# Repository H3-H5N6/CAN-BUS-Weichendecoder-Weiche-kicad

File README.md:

# CAN-BUS Weichendecoder

## Serielle Console
Auf der seriellen Console kann man die Konfiguration einsehen und und die Modul-Id ändern.

Die Serielle Schnittstelle muss dazu auf 115200 gesetzt werden

## Konfigiratuion ansehen

Mit der Taste "p" wird die aktuelle Konfiguartion angezeigt. Beispiel:

```
==== CAN-Konfiguration ====
Version:       1
Status ID:     2
CAN ID: [0] => 811
CAN ID: [1] => 812
CAN ID: [2] => 813
CAN ID: [3] => 814
CAN ID: [4] => 815
CAN ID: [5] => 816
CAN ID: [6] => 817
CAN ID: [7] => 818
CAN ID: [8] => 819
CAN ID: [9] => 820
===========================
```

## Modul-Adresse ändern:

Mit der Eingabe &lt;i> + Nr + &lt;Return> kann die Modul-Adresse geändert werden.

```
Neue ID: 2
Setze neue Id: 2
```

Der Weichendecoder liefert regelmäßig seinen aktuellen Zustand

## Protocol

### IDs

* 100 Frames mit der Id 100 dient dem Verändern des Zustandes
* 200 Sendet den aktuellen Zustand des Decoders, wenn die im ersten Datafeld (u_int16) angegebene Moduladresse mit der des Moduls übereinstimmt. Der Status selbst wird mit der Id 300 gesendet

## CAN-Bus-RJ45-Steckerbelegung

Quelle: https://www.opendcc.de/info/can/can_connector.html

    CAN Pinbelegung auf RJ45
    RJ45 	
    Pin	Signal	    Beschreibung
    1 	CAN_H       Dominant High
    2 	CAN_L    	Dominant Low
    3 	CAN_GND     Ground
    4 	Reserved    Upgrade Path  // DCC A
    5 	Reserved    Upgrade Path  // DCC B
    6 	CAN_SHLD    CAN Shield, Optional
    7 	CAN_GND     Ground
    8 	CAN_V+ 	    Power, Optional

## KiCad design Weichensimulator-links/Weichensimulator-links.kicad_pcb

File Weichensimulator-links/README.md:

# Weichensimulator links

## Releases
### v1.0

* Erster Entwurf

### v2.0

* Fix: Beschreibung der Platine auf der Oberseite, da Relais auf der Leiterseite plaziert wird 
* Change: 90°-Leiterbahnen durch 45° ersetzt

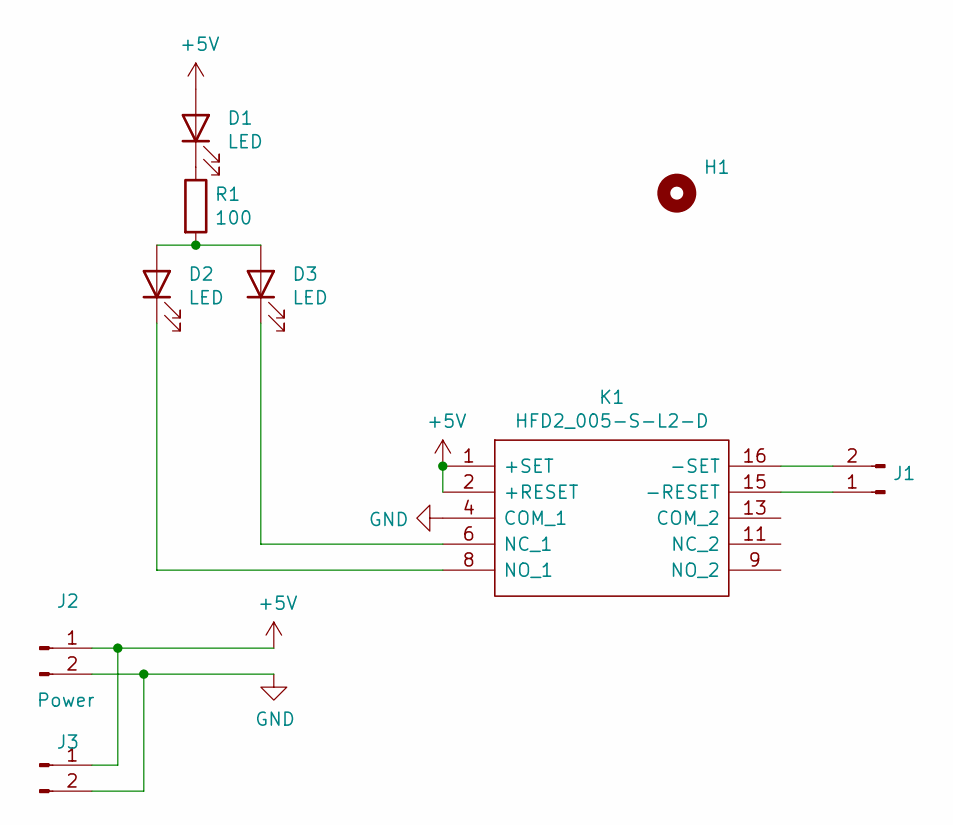
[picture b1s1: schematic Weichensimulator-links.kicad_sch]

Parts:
D1, D2, D3: LED; LED_D5.0mm
H1: MountingHole; MountingHole_3.2mm_M3
J1, J3: Conn_01x02_Male; Pin_Header_Angled_1x02_Pitch2.54mm
J2: Power; Pin_Header_Angled_1x02_Pitch2.54mm
K1: HFD2_005-S-L2-D; HFD2005SL2D; Manufacturer_Part_Number HFD2/005-S-L2-D
R1: 100; R_Axial_DIN0207_L6.3mm_D2.5mm_P7.62mm_Horizontal

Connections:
+5V: D1.2 (A), J2.1, J3.1, K1.1 (+SET), K1.2 (+RESET)
GND: J2.2, J3.2, K1.4 (COM_1)
unnamed: D1.1 (K), R1.1
unnamed: D2.1 (K), K1.8 (NO_1)
unnamed: D2.2 (A), D3.2 (A), R1.2
unnamed: D3.1 (K), K1.6 (NC_1)
unnamed: J1.1, K1.15 (-RESET)
unnamed: J1.2, K1.16 (-SET)

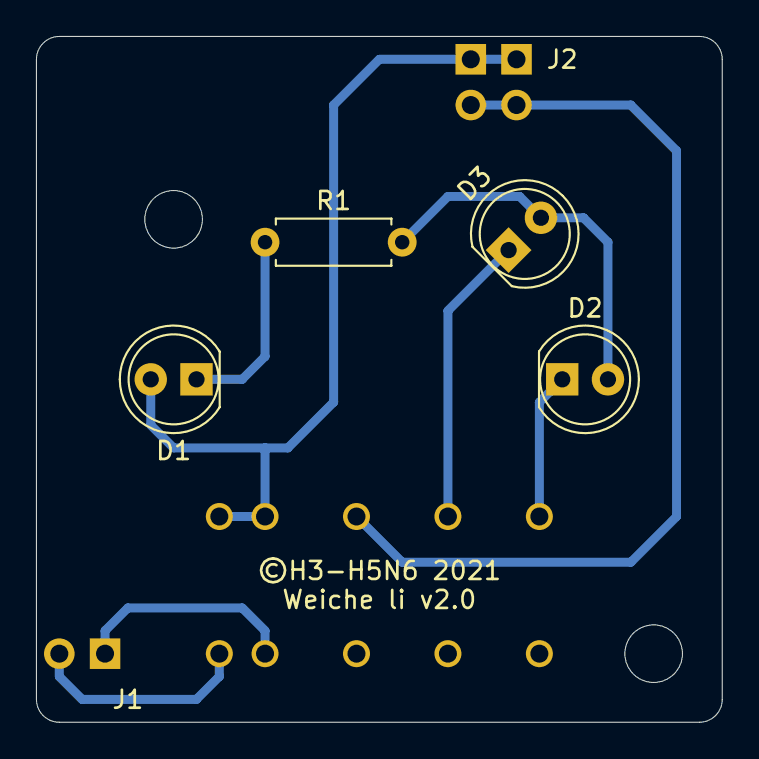
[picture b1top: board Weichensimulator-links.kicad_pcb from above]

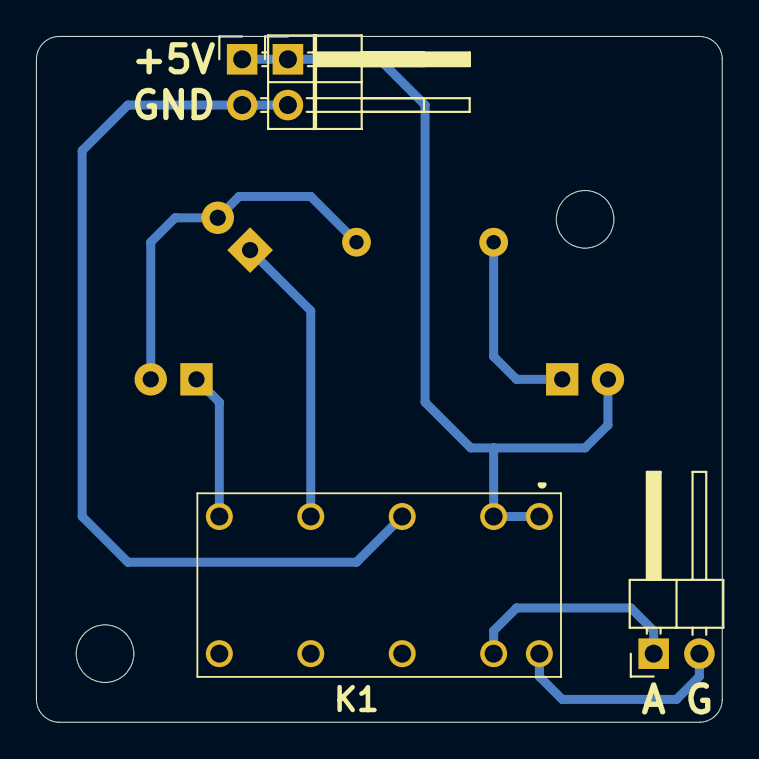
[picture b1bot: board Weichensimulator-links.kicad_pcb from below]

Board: 2 copper layers, 38.1 x 38.1 mm, 10 parts (4 on the bottom side), 8 nets.

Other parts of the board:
H1#2: MountingHole; MountingHole_3.2mm_M3

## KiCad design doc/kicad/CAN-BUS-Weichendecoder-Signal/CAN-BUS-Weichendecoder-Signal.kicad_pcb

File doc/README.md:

# Aktueller Stand (26.11.2021)

Kernstück des Ganzen sind die Weichendecoder für motorische Antriebe mit Impulssteuerung. Zum Einsatz sollen die Antriebe MP6 von MTB kommen. Diese werden mit kurzen Impulse gesteuert, indem der jeweilige Schalteingang kurz gegen Masse gezogen werden. Die Antriebe selbst werden mit 12V DC betrieben und haben auch gleich die Herzstückpolaristaion an Bord.

Geschaltet werden die Schaltausgänge 
* via CAN-BUS (und eigenem Protokoll)
* DCC
* oder für Testzwecke via USB-Console

CAN-BUS, DCC und auch 12V für die Versorgung der eigentlichen Elektronik erfolgt via einem RJ45-Netzwerkkabel.

Für Testzwecke gibt es auch eine kleine CAN-BUS-Zentrale  

Über die Eingabe von einer "Adresse" können die einzelnen Schaltausgänge geschaltet werden. Auch das Schalten von Weichenstraße ist möglich.

Später soll das Ganze durch ein Stellpult mit Schaltern (und LEDs zur Anzeige) ersetzt werden.

Natürlich kann man die Ausgänge auch mit einer gewöhnlichen DCC-Zentrale geschaltet werden. Hier als Beispiel kommt eine ECOS von ESU zu Einsatz, die auch ein Stellpult kennt.

Da aktuell die Anlage ca 120km steht, wurde ein Modellbahn-Simulator gebaut. Die Weichenantriebe sind durch Bistabile Relais nachgebildet und die LED stellen die aktuelle Lage der Weichen wieder.

# CAN-BUS-Frames

Die einzelnen Aktoren haben eine id im Wertebereich uint_16 (2byte)
## Aktor schalten

* Frame ID: 100
* data16: ID1 [, [ID2][, [ID3][, [ID4]]]]

Pro Frame können 4 Aktoren gleichzeit geschaltet werden

## Status der Aktoren

* Frame ID 300
* data16: ID des Aktor, Status des Aktors, unbenutz, ID des aktiven Aktors

### Bedeutung der Status

* OFF 0x00
* ON  0x01
* RUNNING 0x02
* BLOCKED_STATE 0x03
* UNKNOWN_STATE 0x04

Eine einfache Weiche besteht aus zwei Aktoren. Um den Status dieser Weiche zu erhalten, werden zwei Frames gesendet.

Hat der eine Aktor einen Status RUNNING, so hat der zweite Aktor einen Status von BLOCKED_STATE, da dieser aktuell nicht verändert werden kann. 

# Adapter Wannenstecker 2x3 zu Stiftleiste 1x6

## Adapter auf Lochrasterplatte, Ansicht von unten.

## Leiterplatte, Blick von oben auf die Bestückungsseite

## Belegung der 1x6-Stiftleiste, Blick von oben auf die Leiterplatte

6  |  5 |  4 |  3 | 2  | 1 
---|----|----|----|----|---
r1 | r2 | gr |  + | ge | w  

## Belegung des 2x3-Wannensteckers 

5  | 6  | 1  
---|----|----
r2 | r1 | w  
gr | +  | ge 
4  | 3  | 2

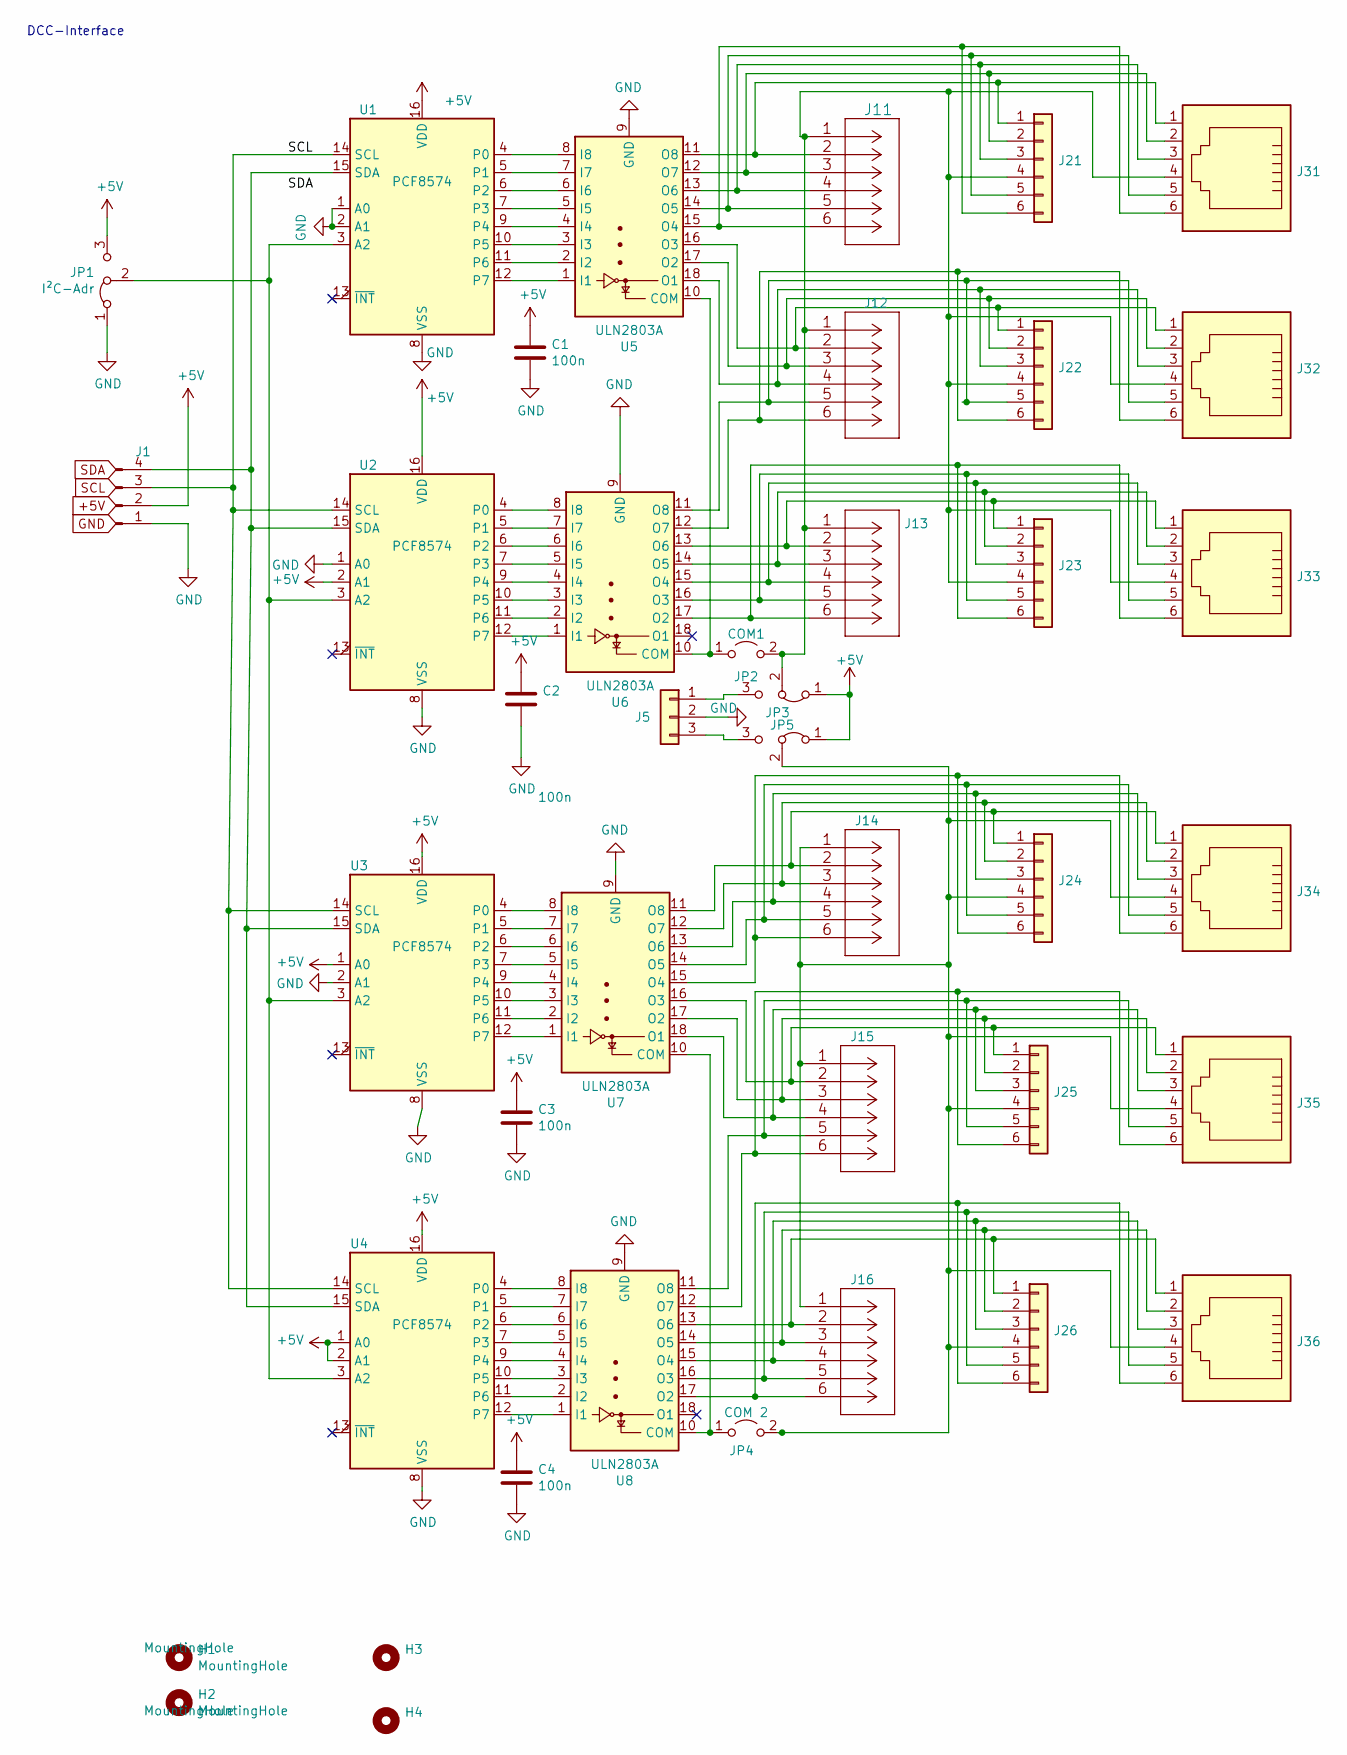
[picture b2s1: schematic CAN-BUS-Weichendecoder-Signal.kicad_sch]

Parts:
C1, C2, C3, C4: 100n; C_Disc_D7.0mm_W2.5mm_P5.00mm
H1, H2, H3, H4: MountingHole; MountingHole_3.2mm_M3
J1: Conn_01x04_Male; Pin_Header_Straight_1x04_Pitch2.54mm
J5: Conn_01x03; TerminalBlock_bornier-3_P5.08mm
J11: 250-1406; CONN_250-1406_WAG_Light
J12, J13, J14, J15, J16: Wago 250-1406; CONN_250-1406_WAG_Light
J21, J22, J23, J24, J25, J26: Conn_01x06; IDC-Header_2x03_P2.54mm_Vertical_Light
J31, J32, J33, J34, J35, J36: RJ12; RJ12_Amphenol_54601_Light
JP1: I²C-Adr; Pin_Header_Straight_1x03_Pitch2.54mm
JP2: COM1; PinHeader_1x02_P2.54mm_Vertical
JP3, JP5: Jumper_3_Bridged12; PinHeader_1x03_P2.54mm_Vertical
JP4: COM 2; PinHeader_1x02_P2.54mm_Vertical
U1, U2, U3, U4: PCF8574; DIP-16_W7.62mm
U5, U6, U7, U8: ULN2803A; DIP-18_W7.62mm

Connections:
unnamed: J1.4, U1.15 (SDA), U2.15 (SDA), U3.15 (SDA), U4.15 (SDA)
unnamed: J5.1, JP3.3 (B)
unnamed: J5.3, JP5.3 (B)
unnamed: J11.1, J12.1, J13.1, J21.4, J22.4, J23.4, J31.4, J32.4, J33.4, JP2.2 (B), JP3.2 (C)
unnamed: J11.2, J21.1, J31.1, U5.11 (O8)
unnamed: J11.3, J21.2, J31.2, U5.12 (O7)
unnamed: J11.4, J21.3, J31.3, U5.13 (O6)
unnamed: J11.5, J21.5, J31.5, U5.14 (O5)
unnamed: J11.6, J21.6, J31.6, U5.15 (O4)
unnamed: J12.2, J22.1, J32.1, U5.16 (O3)
unnamed: J12.3, J22.2, J32.2, U5.17 (O2)
unnamed: J12.4, J22.3, J32.3, U5.18 (O1)
unnamed: J12.5, J22.5, J32.5, U6.11 (O8)
unnamed: J12.6, J22.6, J32.6, U6.12 (O7)
unnamed: J13.2, J23.1, J33.1, U6.13 (O6)
unnamed: J13.3, J23.2, J33.2, U6.14 (O5)
unnamed: J13.4, J23.3, J33.3, U6.15 (O4)
unnamed: J13.5, J23.5, J33.5, U6.16 (O3)
unnamed: J13.6, J23.6, J33.6, U6.17 (O2)
unnamed: J14.1, J15.1, J16.1, J24.4, J25.4, J26.4, J34.4, J35.4, J36.4, JP4.2 (B), JP5.2 (C)
unnamed: J14.2, J24.1, J34.1, U7.11 (O8)
unnamed: J14.3, J24.2, J34.2, U7.12 (O7)
unnamed: J14.4, J24.3, J34.3, U7.13 (O6)
unnamed: J14.5, J24.5, J34.5, U7.14 (O5)
unnamed: J14.6, J24.6, J34.6, U7.15 (O4)
unnamed: J15.2, J25.1, J35.1, U7.16 (O3)
unnamed: J15.3, J25.2, J35.2, U7.17 (O2)
unnamed: J15.4, J25.3, J35.3, U7.18 (O1)
unnamed: J15.5, J25.5, J35.5, U8.11 (O8)
unnamed: J15.6, J25.6, J35.6, U8.12 (O7)
unnamed: J16.2, J26.1, J36.1, U8.13 (O6)
unnamed: J16.3, J26.2, J36.2, U8.14 (O5)
unnamed: J16.4, J26.3, J36.3, U8.15 (O4)
unnamed: J16.5, J26.5, J36.5, U8.16 (O3)
unnamed: J16.6, J26.6, J36.6, U8.17 (O2)
unnamed: JP1.2 (C), U1.3 (A2), U2.3 (A2), U3.3 (A2), U4.3 (A2)
unnamed: JP2.1 (A), U5.10 (COM), U6.10 (COM)
unnamed: JP4.1 (A), U7.10 (COM), U8.10 (COM)
unnamed 39: U1.4 (P0), U5.8 (I8); also elsewhere on the board
unnamed 40: U1.5 (P1), U5.7 (I7); also elsewhere on the board
unnamed 41: U1.6 (P2), U5.6 (I6); also elsewhere on the board
unnamed 42: U1.7 (P3), U5.5 (I5); also elsewhere on the board
unnamed 43: U1.9 (P4), U5.4 (I4); also elsewhere on the board
unnamed 44: U1.10 (P5), U5.3 (I3); also elsewhere on the board
unnamed 45: U1.11 (P6), U5.2 (I2); also elsewhere on the board
unnamed 46: U1.12 (P7), U5.1 (I1); also elsewhere on the board
unnamed 47: U2.4 (P0), U6.8 (I8); also elsewhere on the board
unnamed 48: U2.5 (P1), U6.7 (I7); also elsewhere on the board
unnamed 49: U2.6 (P2), U6.6 (I6); also elsewhere on the board
unnamed 50: U2.7 (P3), U6.5 (I5); also elsewhere on the board
unnamed 51: U2.9 (P4), U6.4 (I4); also elsewhere on the board
unnamed 52: U2.10 (P5), U6.3 (I3); also elsewhere on the board
unnamed 53: U2.11 (P6), U6.2 (I2); also elsewhere on the board
unnamed 54: U2.12 (P7), U6.1 (I1); also elsewhere on the board
unnamed 55: U3.4 (P0), U7.8 (I8); also elsewhere on the board
unnamed 56: U3.5 (P1), U7.7 (I7); also elsewhere on the board
unnamed 57: U3.6 (P2), U7.6 (I6); also elsewhere on the board
unnamed 58: U3.7 (P3), U7.5 (I5); also elsewhere on the board
unnamed 59: U3.9 (P4), U7.4 (I4); also elsewhere on the board
unnamed 60: U3.10 (P5), U7.3 (I3); also elsewhere on the board
unnamed 61: U3.11 (P6), U7.2 (I2); also elsewhere on the board
unnamed 62: U3.12 (P7), U7.1 (I1); also elsewhere on the board
unnamed 63: U4.4 (P0), U8.8 (I8); also elsewhere on the board
unnamed 64: U4.5 (P1), U8.7 (I7); also elsewhere on the board
unnamed 65: U4.6 (P2), U8.6 (I6); also elsewhere on the board
unnamed 66: U4.7 (P3), U8.5 (I5); also elsewhere on the board
unnamed 67: U4.9 (P4), U8.4 (I4); also elsewhere on the board
unnamed 68: U4.10 (P5), U8.3 (I3); also elsewhere on the board
unnamed 69: U4.11 (P6), U8.2 (I2); also elsewhere on the board
unnamed 70: U4.12 (P7), U8.1 (I1); also elsewhere on the board
SCL: J1.3, U1.14 (SCL), U2.14 (SCL), U3.14 (SCL), U4.14 (SCL)

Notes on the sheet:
DCC-Interface

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
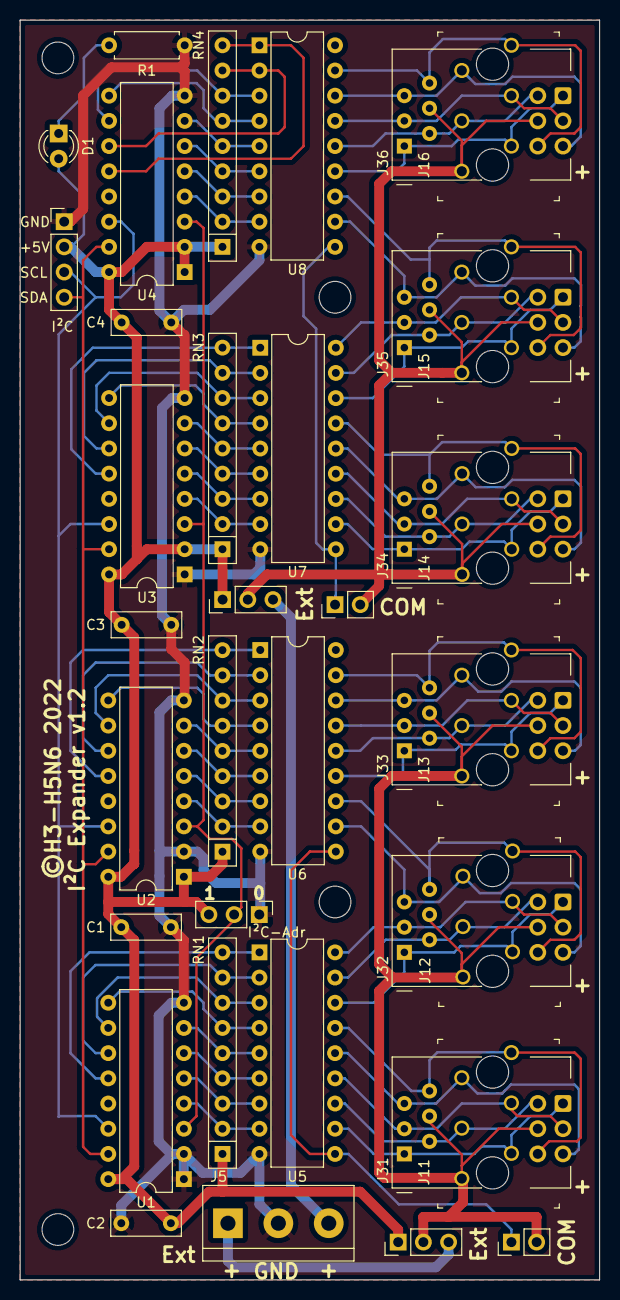
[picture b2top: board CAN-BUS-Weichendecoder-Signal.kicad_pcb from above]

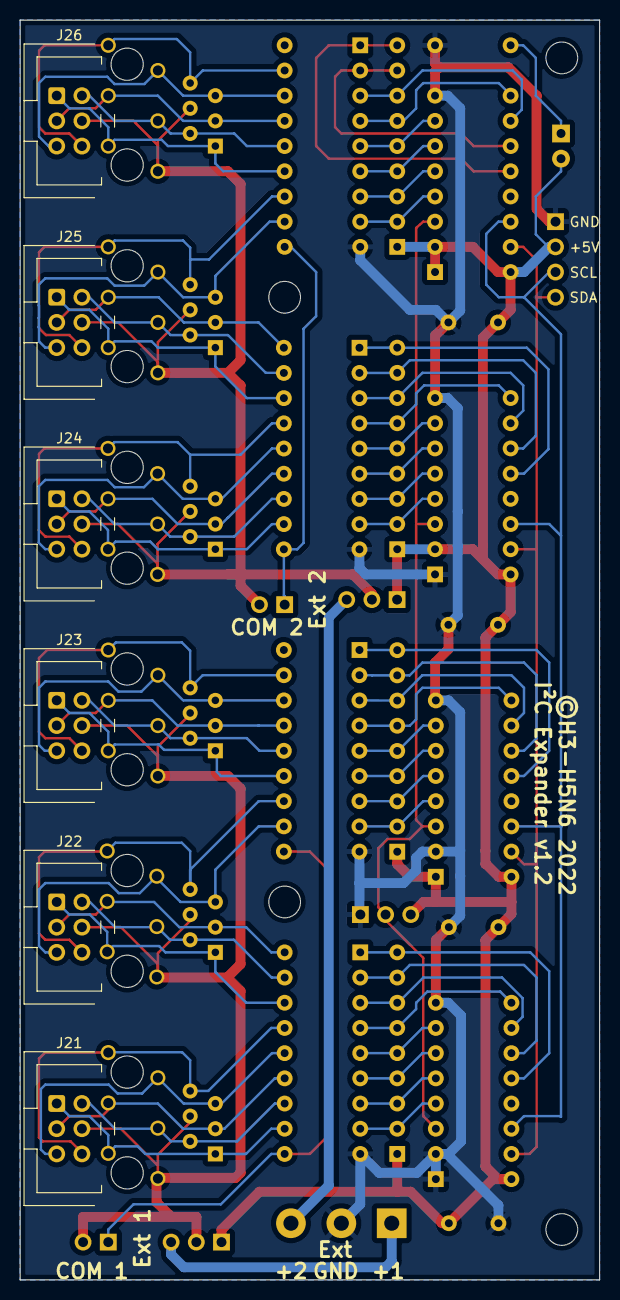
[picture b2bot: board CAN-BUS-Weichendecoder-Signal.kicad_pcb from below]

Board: 2 copper layers, 58.4 x 127.0 mm, 47 parts (6 on the bottom side), 74 nets.

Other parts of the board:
D1: gr; LED_D3.0mm
R1: 1k; R_Axial_DIN0207_L6.3mm_D2.5mm_P7.62mm_Horizontal
RN1, RN2, RN3, RN4: 680; R_Array_SIP9

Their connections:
unnamed: D1.1 (K), R1.1
unnamed 39: RN1.2 (R1); also elsewhere on the board
unnamed 40: RN1.3 (R2); also elsewhere on the board
unnamed 41: RN1.4 (R3); also elsewhere on the board
unnamed 42: RN1.5 (R4); also elsewhere on the board
unnamed 43: RN1.6 (R5); also elsewhere on the board
unnamed 44: RN1.7 (R6); also elsewhere on the board
unnamed 45: RN1.8 (R7); also elsewhere on the board
unnamed 46: RN1.9 (R8); also elsewhere on the board
unnamed 47: RN2.2 (R1); also elsewhere on the board
unnamed 48: RN2.3 (R2); also elsewhere on the board
unnamed 49: RN2.4 (R3); also elsewhere on the board
unnamed 50: RN2.5 (R4); also elsewhere on the board
unnamed 51: RN2.6 (R5); also elsewhere on the board
unnamed 52: RN2.7 (R6); also elsewhere on the board
unnamed 53: RN2.8 (R7); also elsewhere on the board
unnamed 54: RN2.9 (R8); also elsewhere on the board
unnamed 55: RN3.2 (R1); also elsewhere on the board
unnamed 56: RN3.3 (R2); also elsewhere on the board
unnamed 57: RN3.4 (R3); also elsewhere on the board
unnamed 58: RN3.5 (R4); also elsewhere on the board
unnamed 59: RN3.6 (R5); also elsewhere on the board
unnamed 60: RN3.7 (R6); also elsewhere on the board
unnamed 61: RN3.8 (R7); also elsewhere on the board
unnamed 62: RN3.9 (R8); also elsewhere on the board
unnamed 63: RN4.2 (R1); also elsewhere on the board
unnamed 64: RN4.3 (R2); also elsewhere on the board
unnamed 65: RN4.4 (R3); also elsewhere on the board
unnamed 66: RN4.5 (R4); also elsewhere on the board
unnamed 67: RN4.6 (R5); also elsewhere on the board
unnamed 68: RN4.7 (R6); also elsewhere on the board
unnamed 69: RN4.8 (R7); also elsewhere on the board
unnamed 70: RN4.9 (R8); also elsewhere on the board

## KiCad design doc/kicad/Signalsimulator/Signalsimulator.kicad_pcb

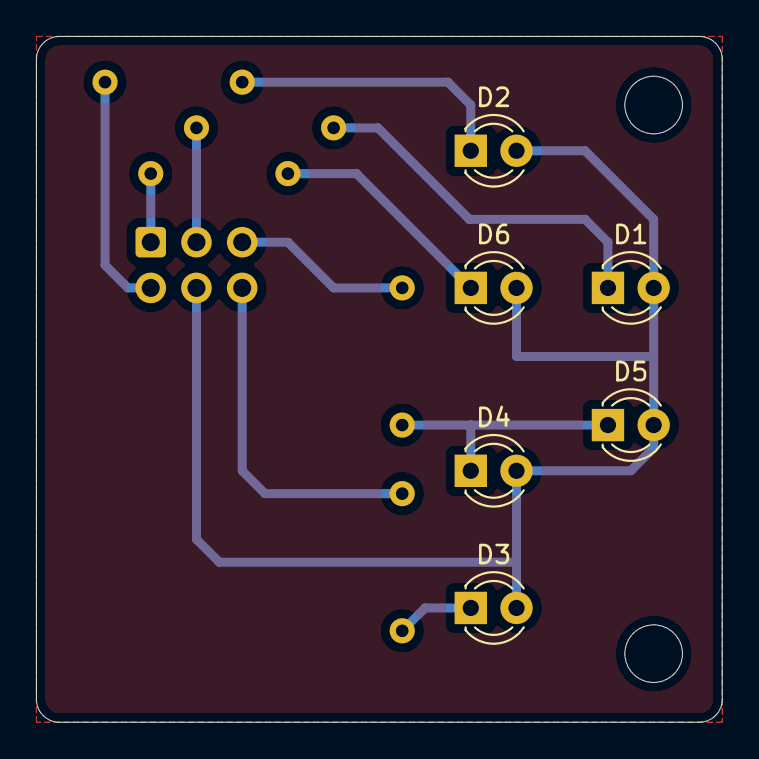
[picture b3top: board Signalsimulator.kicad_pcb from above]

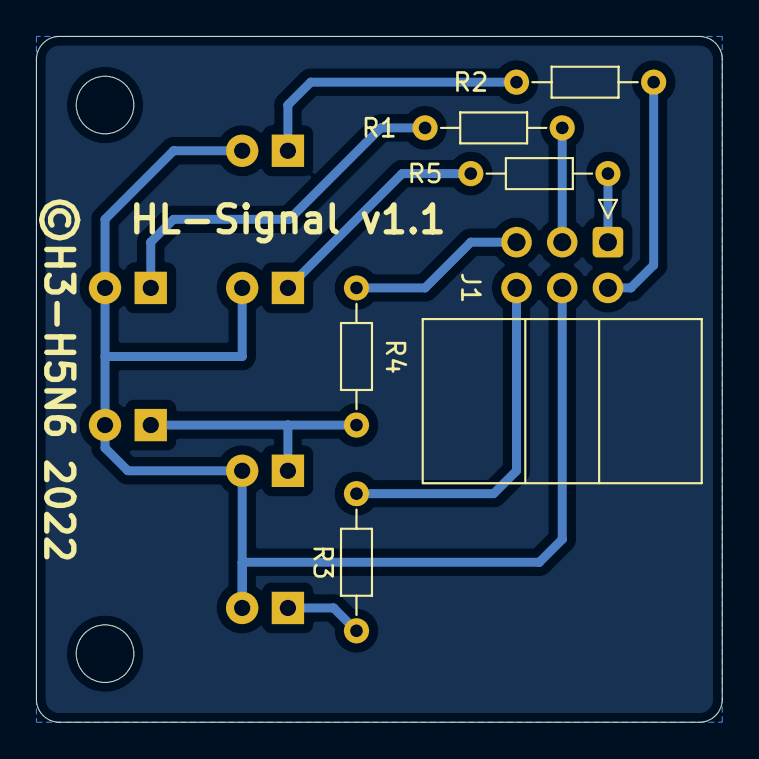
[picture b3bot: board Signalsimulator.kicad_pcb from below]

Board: 2 copper layers, 38.1 x 38.1 mm, 14 parts (6 on the bottom side), 11 nets.

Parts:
D1: Rot 2; LED_D3.0mm
D2: Grün; LED_D3.0mm
D3: Gelb; LED_D3.0mm
D4, D5: Weiß; LED_D3.0mm
D6: Rot 1; LED_D3.0mm
H1, H1#2: MountingHole; MountingHole_3.2mm_M3
J1: Conn_02x03_Odd_Even; IDC-Header_2x03_P2.54mm_Horizontal
R1, R2, R3, R4, R5: R; R_Axial_DIN0204_L3.6mm_D1.6mm_P7.62mm_Horizontal

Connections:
+5P: D1.2, D2.2, D3.2, D4.2, D5.2, D6.2, J1.4
unnamed: D1.1, R1.1
unnamed: D2.1, R2.1
unnamed: D3.1, R3.1
unnamed: D4.1, D5.1, R4.1
unnamed: D6.1, R5.1
unnamed: J1.1, R5.2
unnamed: J1.2, R2.2
unnamed: J1.3, R1.2
unnamed: J1.5, R4.2
unnamed: J1.6, R3.2

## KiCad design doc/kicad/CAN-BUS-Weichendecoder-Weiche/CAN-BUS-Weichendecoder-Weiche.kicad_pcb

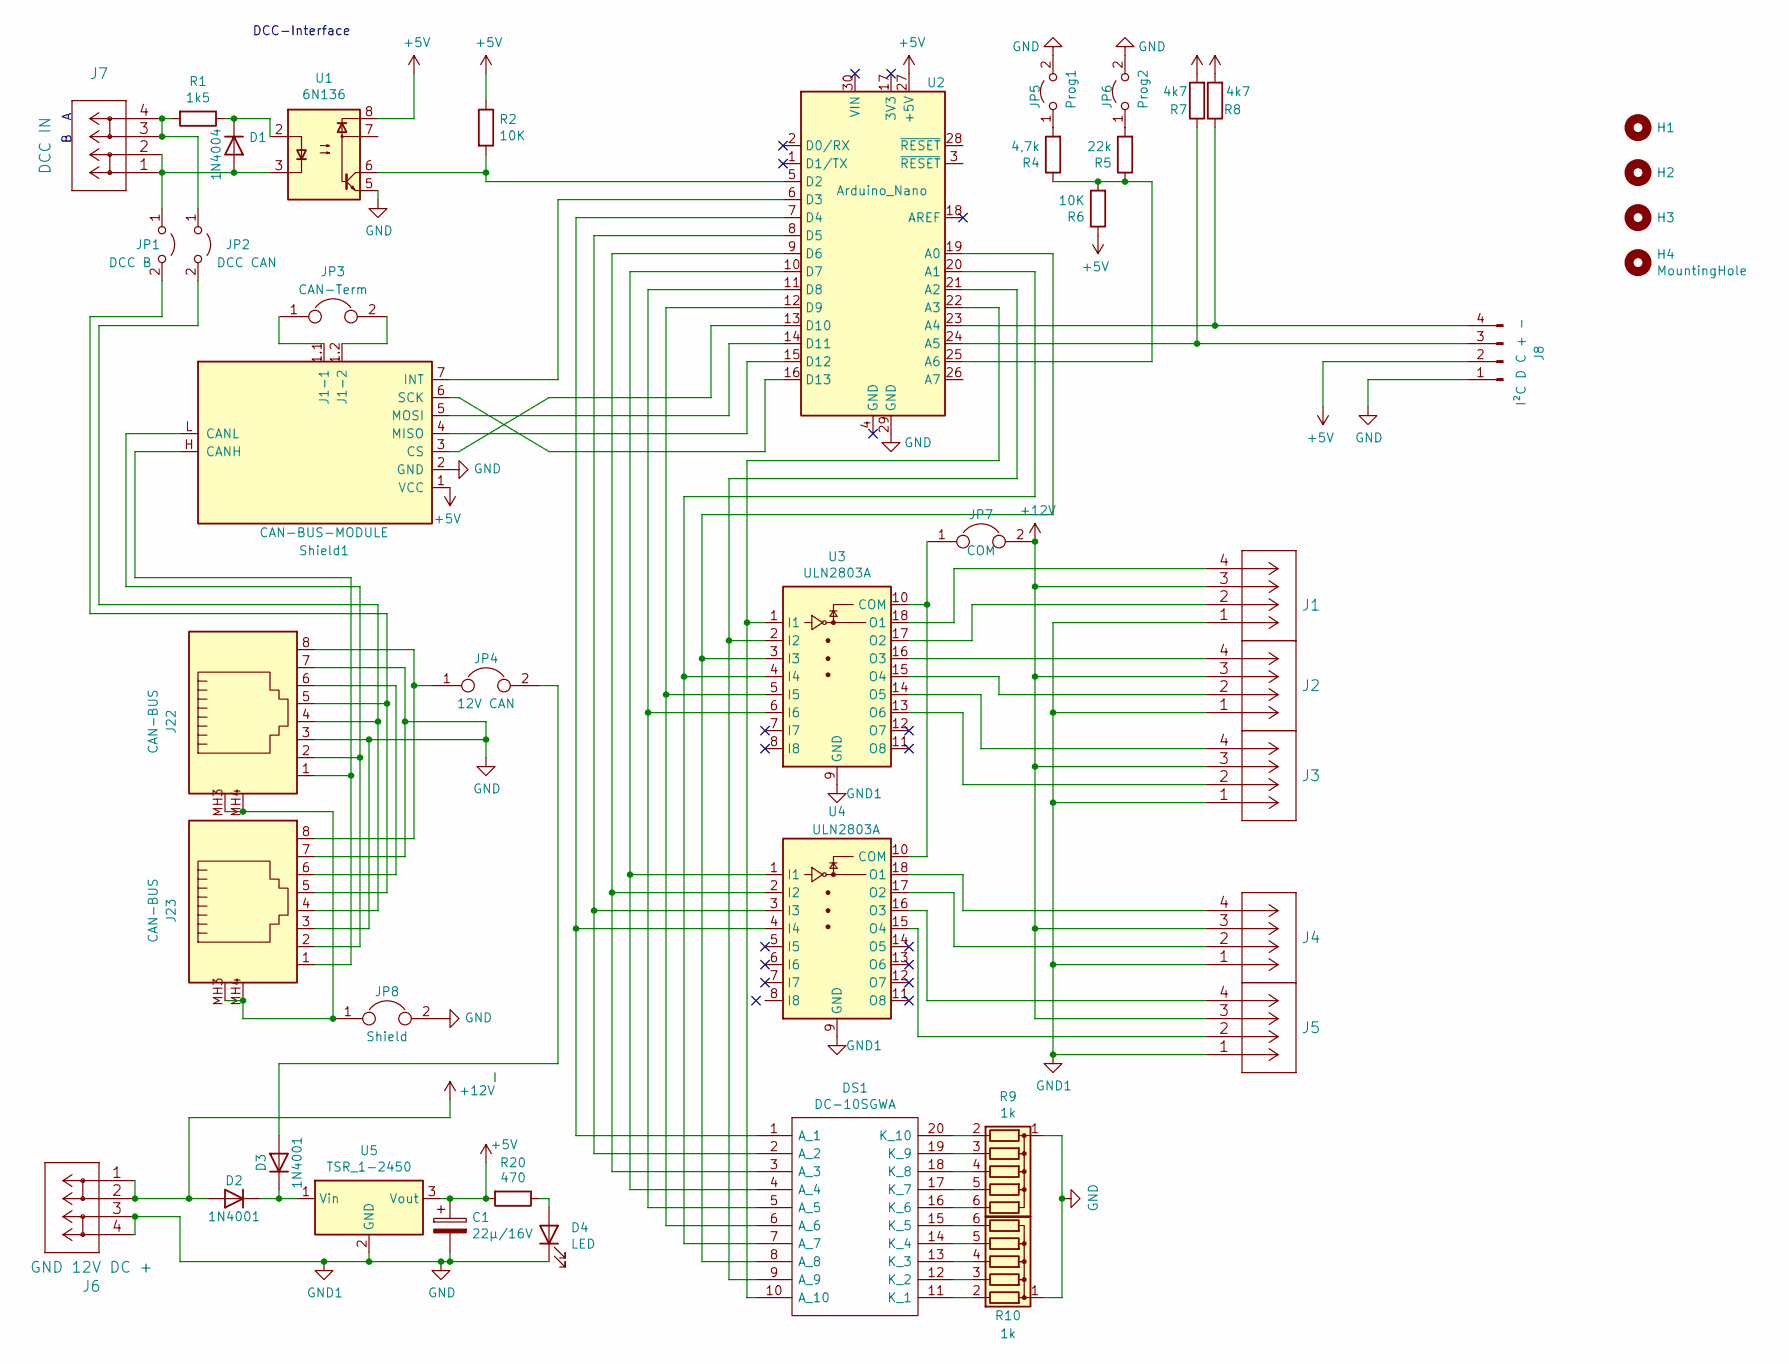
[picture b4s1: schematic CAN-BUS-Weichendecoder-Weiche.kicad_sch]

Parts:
C1: 22µ/16V; CP_Radial_D4.0mm_P1.50mm
D1: 1N4004; D_DO-15_P10.16mm_Horizontal
D2, D3: 1N4001; D_DO-41_SOD81_P7.62mm_Horizontal
D4: LED; LED_D3.0mm
DS1: DC-10SGWA; DIPS750W80P254L2540H825Q20N; Manufacturer_Part_Number DC-10SGWA; Mouser Part Number N/A
H1, H2, H3, H4: MountingHole; MountingHole_3.2mm_M3
J1, J2, J3, J4, J5: 250-1404; CONN_250-1404_WAG
J6: GND 12V DC +; CONN_2604-1102_4_WAG
J7: DCC IN; CONN_2604-1102_4_WAG
J8: I²C D C + -; Pin_Header_Straight_1x04_Pitch2.54mm
J22, J23: CAN-BUS; A20042LPFS
JP1: DCC B; Pin_Header_Straight_1x02_Pitch2.54mm
JP2: DCC CAN; Pin_Header_Straight_1x02_Pitch2.54mm
JP3: CAN-Term; Pin_Header_Straight_1x02_Pitch2.54mm
JP4: 12V CAN; Pin_Header_Straight_1x02_Pitch2.54mm
JP5: Prog1; Pin_Header_Straight_1x02_Pitch2.54mm
JP6: Prog2; Pin_Header_Straight_1x02_Pitch2.54mm
JP7: COM; Pin_Header_Straight_1x02_Pitch2.54mm
JP8: Shield; Pin_Header_Straight_1x02_Pitch2.54mm
R1: 1k5; R_Axial_DIN0207_L6.3mm_D2.5mm_P7.62mm_Horizontal
R2, R6: 10K; R_Axial_DIN0207_L6.3mm_D2.5mm_P7.62mm_Horizontal
R4: 4,7k; R_Axial_DIN0207_L6.3mm_D2.5mm_P7.62mm_Horizontal
R5: 22k; R_Axial_DIN0207_L6.3mm_D2.5mm_P7.62mm_Horizontal
R7, R8: 4k7; R_Axial_DIN0207_L6.3mm_D2.5mm_P7.62mm_Horizontal
R9, R10: 1k; R_Array_SIP6
R20: 470; R_Axial_DIN0207_L6.3mm_D2.5mm_P7.62mm_Horizontal
Shield1: CAN-BUS-MODULE; MCP2515_CAN_MODULE
U1: 6N136; DIP-8_W7.62mm
U2: Arduino_Nano
U3, U4: ULN2803A; DIP-18_W7.62mm
U5: TSR_1-2450; DCDC-Conv_TRACO_TSR-1

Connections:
+5V: C1.1, J8.2, R2.1, R6.1, R7.2, R8.2, R20.2, Shield1.1 (VCC), U1.8, U2.27 (+5V), U5.3 (Vout)
+12V: D2.2 (A), J1.3, J2.3, J3.3, J4.3, J5.3, J6.1, J6.2, JP7.2
GND: C1.2, D4.1 (K), J1.1, J2.1, J3.1, J4.1, J5.1, J6.3, J6.4, J8.1, J22.3, J22.7, J23.3, J23.7, JP5.2 (B), JP6.2 (B), JP8.2, R9.1 (common), R10.1 (common), Shield1.2 (GND), U1.5, U2.29 (GND), U3.9 (GND), U4.9 (GND), U5.2 (GND)
unnamed: D1.1 (K), R1.1, U1.2
unnamed: D1.2 (A), J7.1, J7.2, JP1.1 (A), U1.3
unnamed: D2.1 (K), D3.1 (K), U5.1 (Vin)
unnamed: D3.2 (A), JP4.2
unnamed: D4.2 (A), R20.1
unnamed: DS1.1 (A_1), U2.7 (D4), U4.4 (I4)
unnamed: DS1.2 (A_2), U2.8 (D5), U4.3 (I3)
unnamed: DS1.3 (A_3), U2.9 (D6), U4.2 (I2)
unnamed: DS1.4 (A_4), U2.10 (D7), U4.1 (I1)
unnamed: DS1.5 (A_5), U2.11 (D8), U3.6 (I6)
unnamed: DS1.6 (A_6), U2.12 (D9), U3.5 (I5)
unnamed: DS1.7 (A_7), U2.20 (A1), U3.4 (I4)
unnamed: DS1.8 (A_8), U2.19 (A0), U3.3 (I3)
unnamed: DS1.9 (A_9), U2.21 (A2), U3.2 (I2)
unnamed: DS1.10 (A_10), U2.22 (A3), U3.1 (I1)
unnamed: DS1.11 (K_1), R10.2 (R1)
unnamed: DS1.12 (K_2), R10.3 (R2)
unnamed: DS1.13 (K_3), R10.4 (R3)
unnamed: DS1.14 (K_4), R10.5 (R4)
unnamed: DS1.15 (K_5), R10.6 (R5)
unnamed: DS1.16 (K_6), R9.6 (R5)
unnamed: DS1.17 (K_7), R9.5 (R4)
unnamed: DS1.18 (K_8), R9.4 (R3)
unnamed: DS1.19 (K_9), R9.3 (R2)
unnamed: DS1.20 (K_10), R9.2 (R1)
unnamed: J1.2, U3.17 (O2)
unnamed: J1.4, U3.18 (O1)
unnamed: J2.2, U3.15 (O4)
unnamed: J2.4, U3.16 (O3)
unnamed: J3.2, U3.13 (O6)
unnamed: J3.4, U3.14 (O5)
unnamed: J4.2, U4.17 (O2)
unnamed: J4.4, U4.18 (O1)
unnamed: J5.2, U4.15 (O4)
unnamed: J5.4, U4.16 (O3)
unnamed: J7.3, J7.4, JP2.1 (A), R1.2
unnamed: J8.3, R7.1, U2.24 (A5)
unnamed: J8.4, R8.1, U2.23 (A4)
unnamed: J22.1, J23.1, Shield1.H (CANH)
unnamed: J22.2, J23.2, Shield1.L (CANL)
unnamed: J22.4, J23.4, JP2.2 (B)
unnamed: J22.5, J23.5, JP1.2 (B)
unnamed: J22.6, J23.6
unnamed: J22.8, J23.8, JP4.1
unnamed: J22.MH3, J22.MH4, J23.MH3, J23.MH4, JP8.1
unnamed: JP3.1, Shield1.1.1 (J1-1)
unnamed: JP3.2, Shield1.1.2 (J1-2)
unnamed: JP5.1 (A), R4.2
unnamed: JP6.1 (A), R5.2
unnamed: JP7.1, U3.10 (COM), U4.10 (COM)
unnamed: R2.2, U1.6, U2.5 (D2)
unnamed: R4.1, R5.1, R6.2, U2.25 (A6)
unnamed: Shield1.3 (CS), U2.13 (D10)
unnamed: Shield1.4 (MISO), U2.15 (D12)
unnamed: Shield1.5 (MOSI), U2.14 (D11)
unnamed: Shield1.6 (SCK), U2.16 (D13)
unnamed: Shield1.7 (INT), U2.6 (D3)

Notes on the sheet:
DCC-Interface
B A

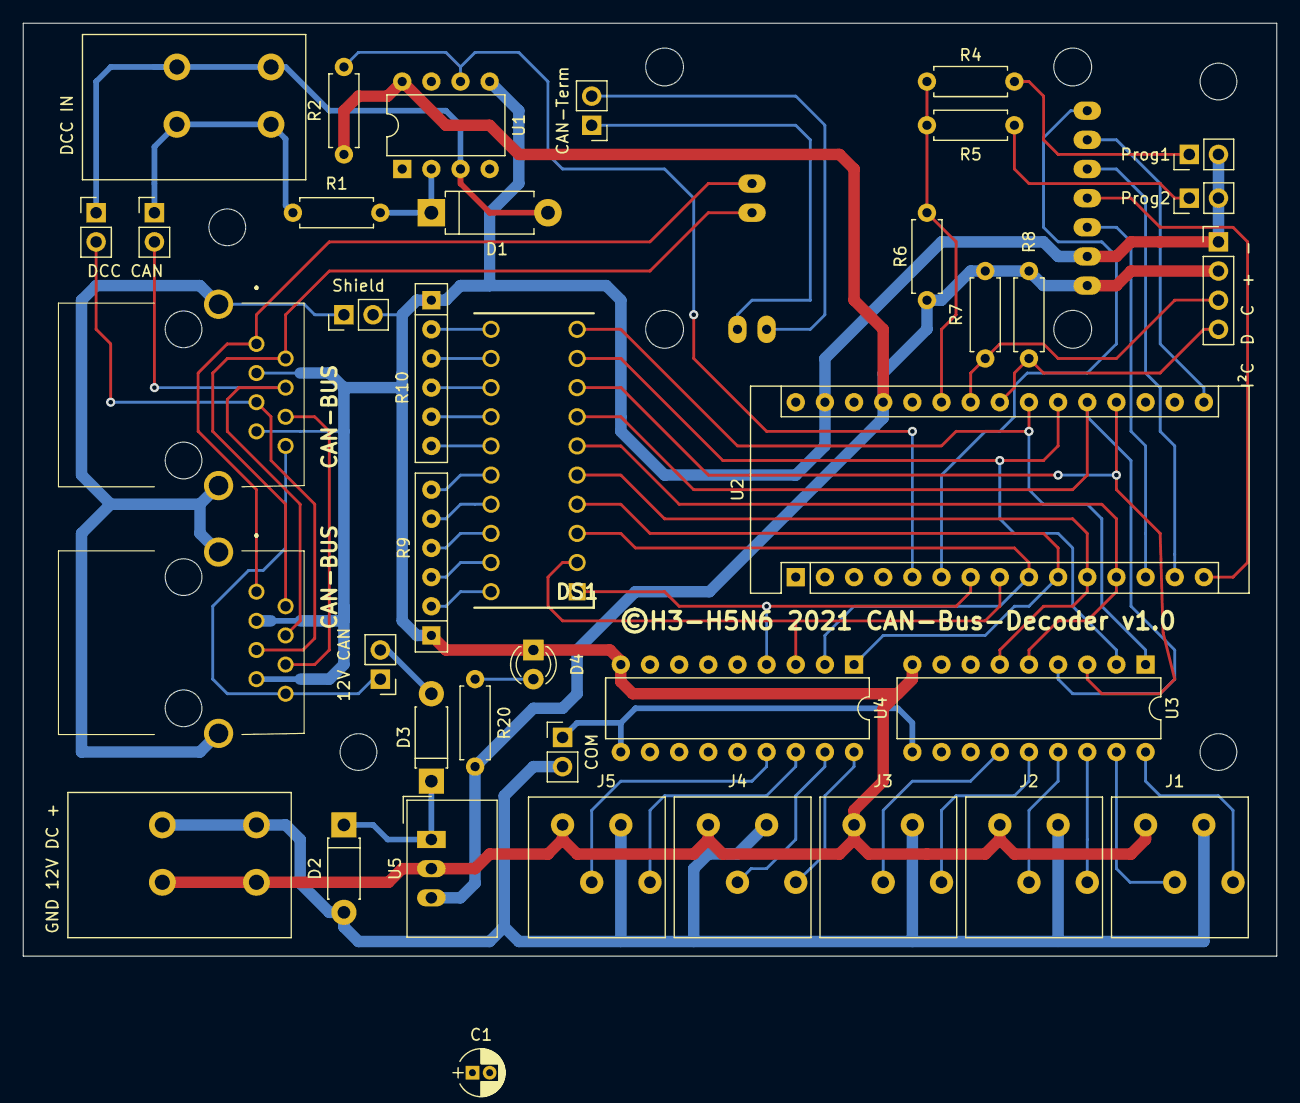
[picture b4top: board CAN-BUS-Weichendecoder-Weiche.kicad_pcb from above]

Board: 2 copper layers, 109.2 x 81.3 mm, 44 parts (1 on the bottom side), 60 nets.

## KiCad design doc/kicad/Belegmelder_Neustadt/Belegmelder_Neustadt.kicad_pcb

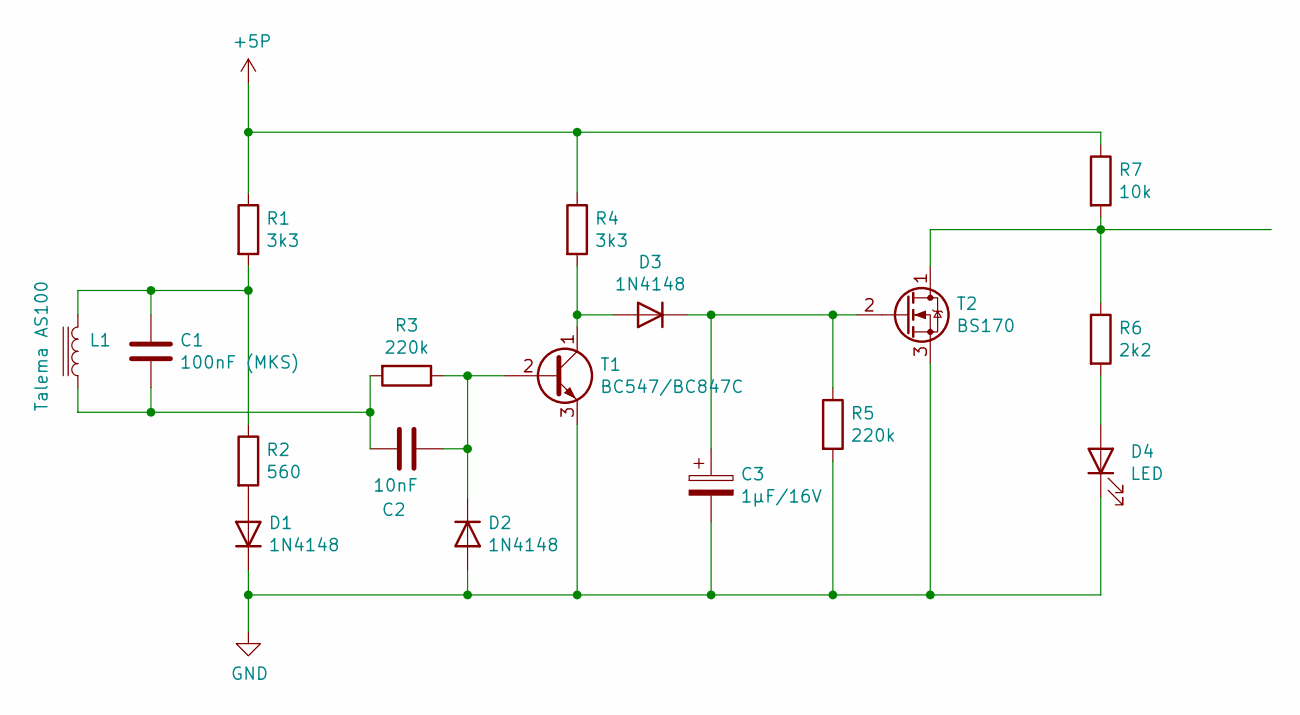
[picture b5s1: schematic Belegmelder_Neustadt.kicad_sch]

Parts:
C1: 100nF (MKS); C_2220
C2: 10nF; C_0805
C3: 1µF/16V; CP_Elec_4x5.3
D1, D2, D3: 1N4148; D_SOD-323F
D4: LED; LED_0805
L1: Talema AS100; AS-1xx
R1, R4: 3k3; R_0805
R2: 560; R_0805
R3, R5: 220k; R_0805
R6: 2k2; R_0805
R7: 10k; R_0805
T1: BC547/BC847C; SOT-23
T2: BS170; SOT-23

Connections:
+5P: R1.1, R4.1, R7.1
GND: C3.2, D1.1 (K), D2.2 (A), D4.1 (K), R5.2, T1.3 (E), T2.3 (S)
unnamed: C1.1, C2.1, L1.1, R3.2
unnamed: C1.2, L1.2, R1.2, R2.1
unnamed: C2.2, D2.1 (K), R3.1, T1.2 (B)
unnamed: C3.1, D3.1 (K), R5.1, T2.2 (G)
unnamed: D1.2 (A), R2.2
unnamed: D3.2 (A), R4.2, T1.1 (C)
unnamed: D4.2 (A), R6.2
unnamed: R6.1, R7.2, T2.1 (D)

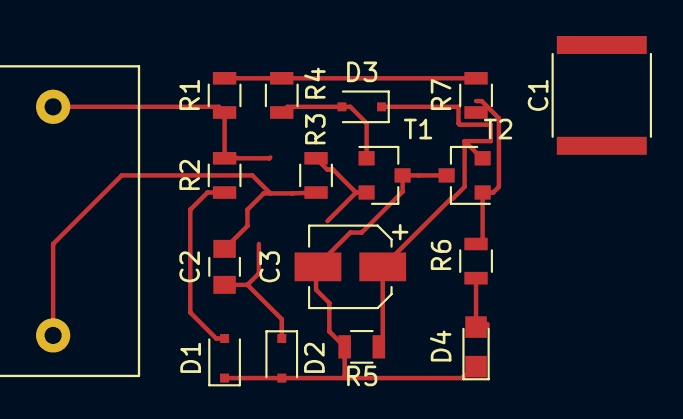
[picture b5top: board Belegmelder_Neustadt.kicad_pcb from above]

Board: 2 copper layers, 17 parts (0 on the bottom side), 10 nets.

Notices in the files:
Weichensimulator-links/Weichensimulator-links.kicad_pcb:
©H3-H5N6 2021
doc/kicad/CAN-BUS-Weichendecoder-Signal/CAN-BUS-Weichendecoder-Signal.kicad_pcb:
©H3-H5N6 2022
doc/kicad/CAN-BUS-Weichendecoder-Weiche/CAN-BUS-Weichendecoder-Weiche.kicad_pcb:
©H3-H5N6 2021 CAN-Bus-Decoder v1.0
parts and their libraries:
Copyright 2021 Accelerated Designs. All rights reserved.
